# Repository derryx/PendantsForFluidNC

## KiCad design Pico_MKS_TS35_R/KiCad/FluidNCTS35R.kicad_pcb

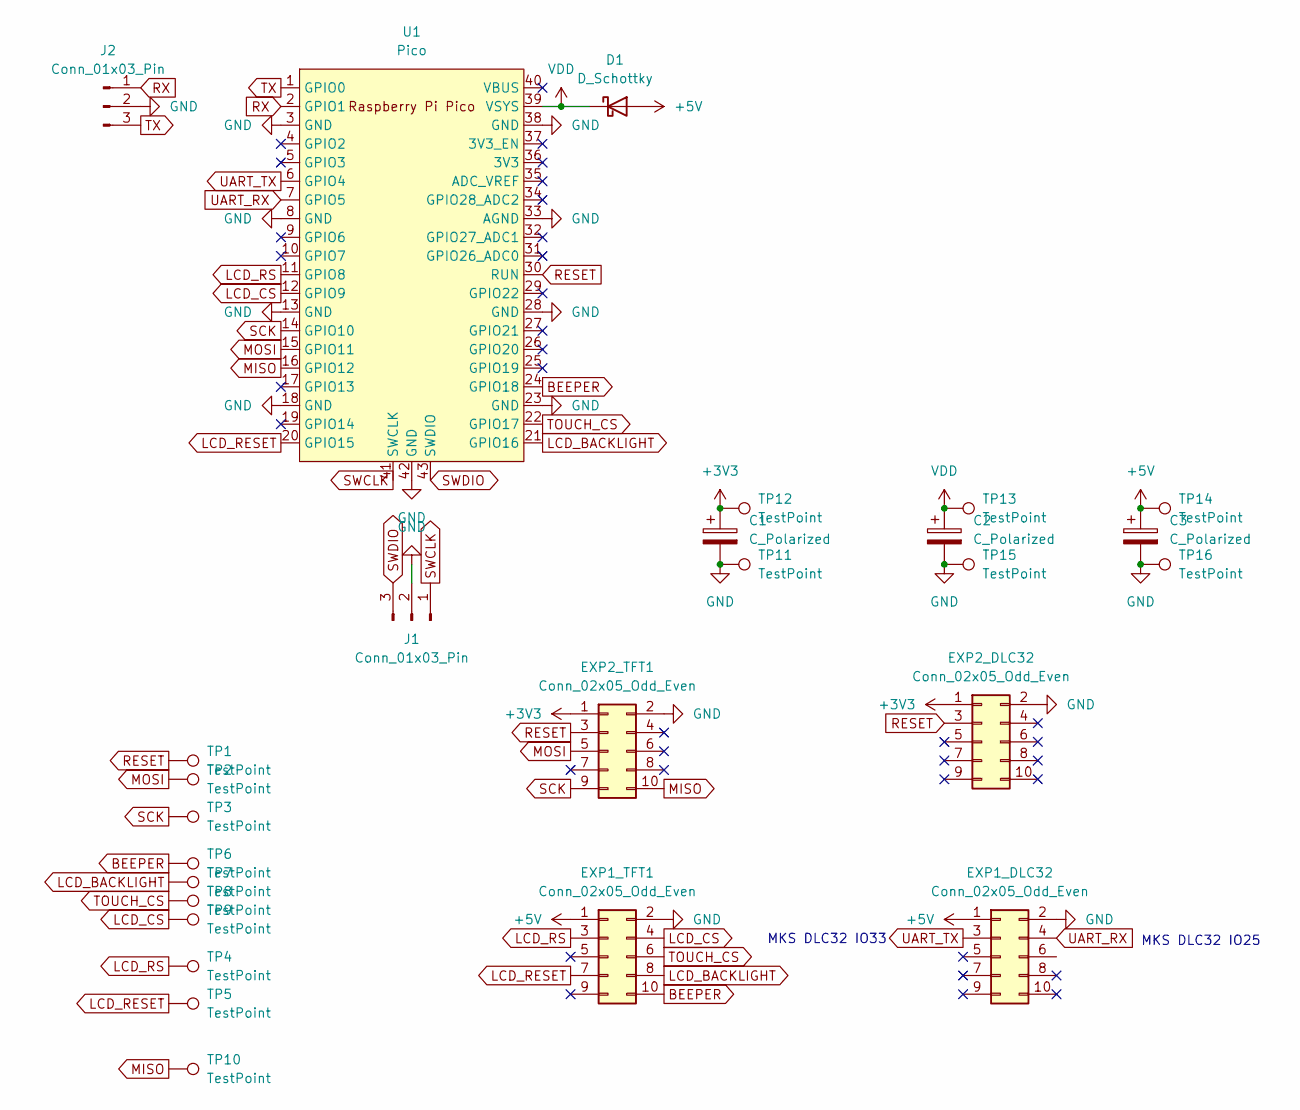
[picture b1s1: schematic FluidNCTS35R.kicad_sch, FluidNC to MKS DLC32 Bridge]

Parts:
C1, C2, C3: C_Polarized; C_1210_3225Metric_Pad1.33x2.70mm_HandSolder
D1: D_Schottky; D_SOD-123
EXP1_DLC32, EXP1_TFT1, EXP2_DLC32, EXP2_TFT1: Conn_02x05_Odd_Even; IDC-Header_2x05_P2.54mm_Vertical
J1: Conn_01x03_Pin; PinSocket_1x03_P2.54mm_Horizontal
J2: Conn_01x03_Pin; PinHeader_1x03_P2.54mm_Horizontal
TP1, TP2, TP3, TP4, TP5, TP6, TP7, TP8, TP9, TP10, TP11, TP12, TP13, TP14, TP15, TP16: TestPoint; TestPoint_Pad_D2.0mm
U1: Pico; RPi_Pico_SMD_TH

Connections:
+3V3: C1.1, EXP2_DLC32.1, EXP2_TFT1.1, TP12.1
+5V: C3.1, D1.2 (A), EXP1_DLC32.1, EXP1_TFT1.1, TP14.1
BEEPER: EXP1_TFT1.10, TP6.1, U1.24 (GPIO18)
GND: C1.2, C2.2, C3.2, EXP1_DLC32.2, EXP1_TFT1.2, EXP2_DLC32.2, EXP2_TFT1.2, J1.2, J2.2, TP11.1, TP15.1, TP16.1, U1.3 (GND), U1.8 (GND), U1.13 (GND), U1.18 (GND), U1.23 (GND), U1.28 (GND), U1.33 (AGND), U1.38 (GND), U1.42 (GND)
LCD_BACKLIGHT: EXP1_TFT1.8, TP7.1, U1.21 (GPIO16)
LCD_CS: EXP1_TFT1.4, TP9.1, U1.12 (GPIO9)
LCD_RESET: EXP1_TFT1.7, TP5.1, U1.20 (GPIO15)
LCD_RS: EXP1_TFT1.3, TP4.1, U1.11 (GPIO8)
MISO: EXP2_TFT1.10, TP10.1, U1.16 (GPIO12)
MOSI: EXP2_TFT1.5, TP2.1, U1.15 (GPIO11)
RESET: EXP2_DLC32.3, EXP2_TFT1.3, TP1.1, U1.30 (RUN)
RX: J2.1, U1.2 (GPIO1)
SCK: EXP2_TFT1.9, TP3.1, U1.14 (GPIO10)
SWCLK: J1.1, U1.41 (SWCLK)
SWDIO: J1.3, U1.43 (SWDIO)
TOUCH_CS: EXP1_TFT1.6, TP8.1, U1.22 (GPIO17)
TX: J2.3, U1.1 (GPIO0)
UART_RX: EXP1_DLC32.4, U1.7 (GPIO5)
UART_TX: EXP1_DLC32.3, U1.6 (GPIO4)
VDD: C2.1, D1.1 (K), TP13.1, U1.39 (VSYS)

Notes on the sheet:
MKS DLC32 IO33
MKS DLC32 IO25

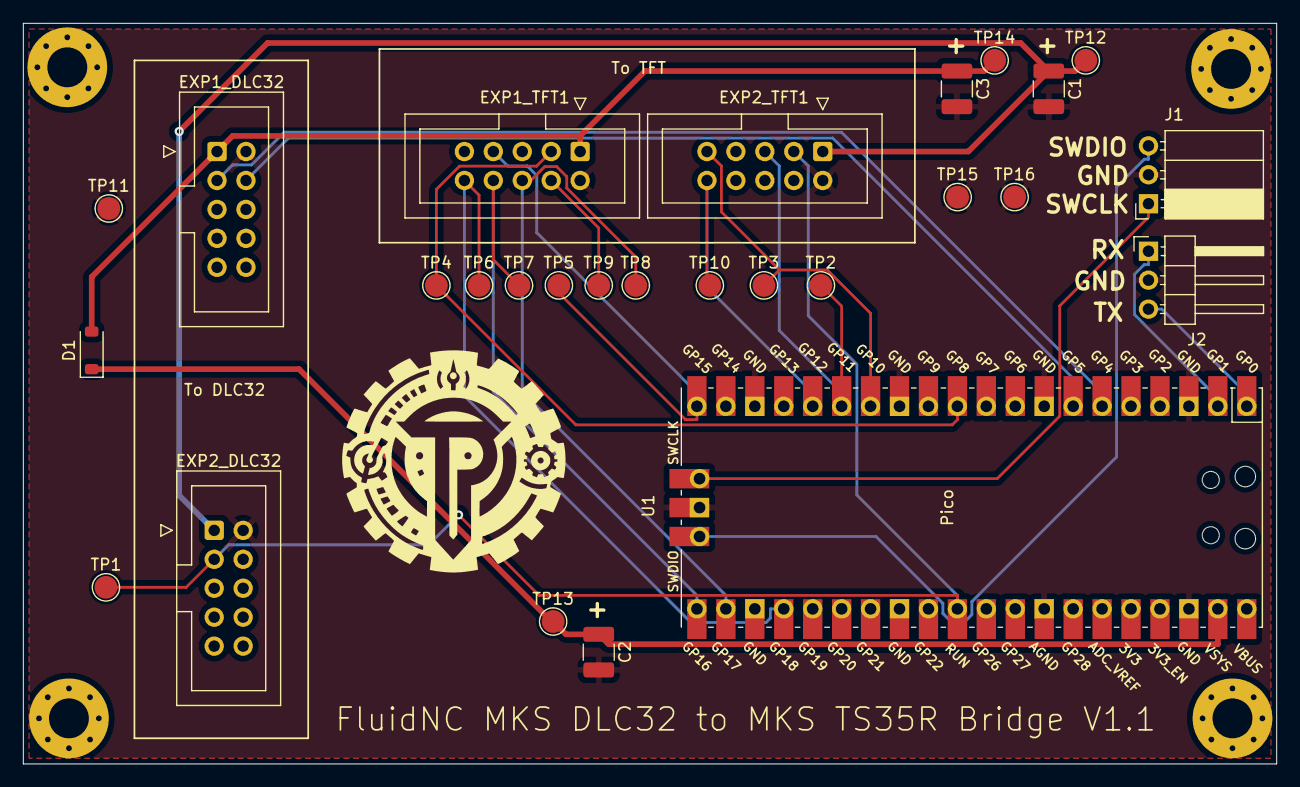
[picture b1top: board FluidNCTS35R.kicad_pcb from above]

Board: 2 copper layers, 110.0 x 65.0 mm, 31 parts (0 on the bottom side), 20 nets.

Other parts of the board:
GND: MountingHole_3.5mm_Pad_Via
Hole1, Hole3, Hole4: MountingHole_3.5mm_Pad_Via

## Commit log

2024-02-19 Add example code
2024-02-21 Add model and ui headers
2024-02-21 First working version with model
2024-02-22 Axis with spans
2024-02-23 Axis look somewhat okay
2024-02-24 Add PCB
2024-02-25 Some styling
2024-02-27 Some real buttons
2024-02-27 Add some buttons depending on state
2024-03-03 Add PCB and some button handlers
2024-03-03 Add some code to send actual commands to FluidNC
2024-03-10 Make buttons work
2024-03-14 buttons work
2024-04-21 Updated Board. Use GPIO 33 as input
2024-09-22 Upgrade to latest LVGL
2025-05-28 Updated to LVGL 9.2.0
2025-09-30 Updated to LVGL 9.3.3
